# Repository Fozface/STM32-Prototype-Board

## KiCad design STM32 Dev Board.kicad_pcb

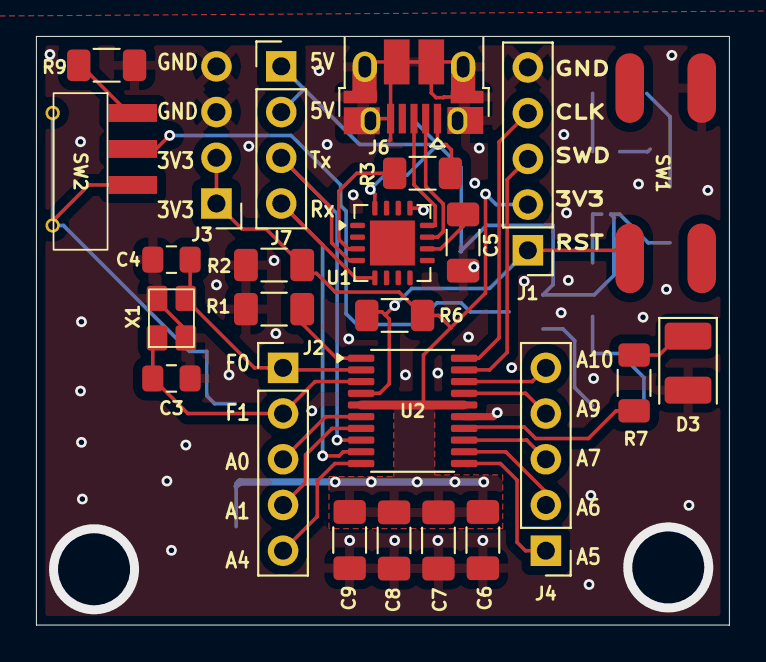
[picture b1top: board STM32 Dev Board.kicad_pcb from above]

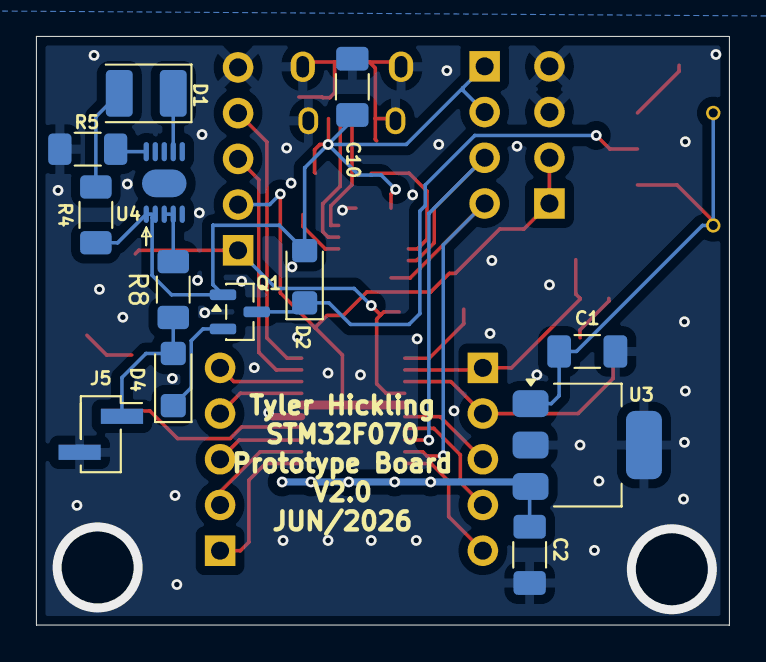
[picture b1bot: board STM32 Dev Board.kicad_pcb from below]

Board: 2 copper layers, 38.5 x 32.7 mm, 38 parts (13 on the bottom side), 34 nets.

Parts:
C1, C7: 4.7uF; C_1206_3216Metric_Pad1.33x1.80mm_HandSolder
C2: 1uF; C_1206_3216Metric_Pad1.33x1.80mm_HandSolder
C3, C4: 7pF; C_0805_2012Metric_Pad1.18x1.45mm_HandSolder
C5: 0.22-0.47u; C_1206_3216Metric_Pad1.33x1.80mm_HandSolder
C6: 100nF; C_1206_3216Metric_Pad1.33x1.80mm_HandSolder
C8: 10nF; C_1206_3216Metric_Pad1.33x1.80mm_HandSolder
C9: 1u; C_1206_3216Metric_Pad1.33x1.80mm_HandSolder
C10: 5u; C_1206_3216Metric_Pad1.33x1.80mm_HandSolder
D1: LED; LED_PLCC-2_3.4x3.0mm_KA
D2: D_Schottky; D_SMF
D3: LED; LED_PLCC-2_3.4x3.0mm_AK
D4: V1FM10-M3/H; D_SMF
J1, J2, J4: PinHeader_1x05_P2.54mm_Vertical
J3, J7: PinHeader_1x04_P2.54mm_Vertical
J5: 2 Pin JST; PinHeader_1x02_P2.00mm_Vertical_SMD_Pin1Right
J6: USB_B_Micro; USB_Micro-B_Amphenol_10103594-0001LF_Horizontal
Q1: PMOS; SOT-23
R1: 10k; C_1206_3216Metric_Pad1.33x1.80mm_HandSolder
R2: 0; C_1206_3216Metric_Pad1.33x1.80mm_HandSolder
R3, R6, R9: 10k; R_1206_3216Metric_Pad1.30x1.75mm_HandSolder
R4: 250; R_1206_3216Metric_Pad1.30x1.75mm_HandSolder
R5: 6.2k; R_1206_3216Metric_Pad1.30x1.75mm_HandSolder
R7: 330; R_1206_3216Metric_Pad1.30x1.75mm_HandSolder
R8: 0; R_1206_3216Metric_Pad1.30x1.75mm_HandSolder
SW1: SMT button KT Series top
SW2: 450405020524 SW
U1: MCP2221A-I/ML; QFN-16-1EP_4x4mm_P0.65mm_EP2.5x2.5mm
U2: STM32F070F6Px; TSSOP-20_4.4x6.5mm_P0.65mm
U3: MCP1824S; SOT-223-3_TabPin2
U4: MCP73113
X1: Xtal

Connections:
3.3V: C2.1, C6.1, C7.1, C8.1, C9.1, J1.2, J3.1, J3.2, R2.1, R6.1, U2.5 (VDDA), U2.16 (VDD), U3.3 (VO)
/MCU/SWCLK: J1.4, U2.20 (PA14)
/MCU/SWD: J1.3, U2.19 (PA13)
/PSU/BAT+: R8.1, U4.3 (VBAT), U4.4 (VBAT)
/PSU/STAT: D1.1 (K), U4.7 (STAT)
GND: C1.2, C2.2, C3.2, C4.1, C5.2, C6.2, C7.2, C8.2, C9.2, C10.2, D3.1 (K), J1.5, J3.3, J3.4, J5.2, J6.5 (GND), J6.6 (Shield), R1.1, R2.2, R5.2, R9.2, SW1.1, U1.13 (VSS), U2.15 (VSS), U3.2 (GND), U4.8 (VSS), U4.9 (VSS), X1.2 (GND), X1.4 (GND)
unnamed: D1.2 (A), R4.1
unnamed: D2.1 (K), Q1.1 (D), SW2.2
unnamed: D3.2 (A), R7.1
unnamed: D4.2 (A), J5.1, R8.2
unnamed: D4.1 (K), Q1.3 (S)
unnamed: J6.3 (D+), U1.12 (D+)
unnamed: J6.2 (D-), U1.11 (D-)
unnamed: R9.1, SW2.1
unnamed: C1.1, SW2.3 (C), SW2.4 (MNT), U3.1 (VI)
unnamed: C5.1, U1.10 (VUSB)
unnamed: R3.1, U1.3 (~RST)
unnamed: R1.2, U2.1 (BOOT0)
unnamed: J1.1, R6.2, SW1.4, U2.4 (NRST)
unnamed: J2.3, U2.6 (PA0)
unnamed: J2.4, U2.7 (PA1)
unnamed: J2.5, U2.10 (PA4)
unnamed: J4.1, U2.11 (PA5)
unnamed: J4.2, U2.12 (PA6)
unnamed: J4.3, U2.13 (PA7)
unnamed: J4.4, U2.17 (PA9/PA11)
unnamed: J4.5, U2.18 (PA10/PA12)
unnamed: R7.2, U2.14 (PB1)
unnamed: C4.2, J2.1, U2.2 (PF0), X1.3 (Xtal)
unnamed: C3.1, J2.2, U2.3 (PF1), X1.1 (Xtal)
unnamed: R5.1, U4.10 (PROG)
UART_Rx: J7.4, U1.5 (UTx), U2.9 (PA3)
UART_Tx: J7.3, U1.4 (URx), U2.8 (PA2)
VUSB: C10.1, D2.2 (A), J6.1 (VBUS), J7.1, J7.2, Q1.2 (G), R3.2, R4.2, U1.16 (VDD), U4.1 (VDD), U4.2 (VDD)

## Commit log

2026-06-22 Init Commit
2026-06-22 generated BOM
2026-06-22 generated drill and gerber files, updeted a few datasheets
2026-06-22 added gerber and drill files
2026-06-22 added ground via for UART-USB, updated gerber and drill files
2026-06-22 changed R8 FP to match component
2026-06-22 moved R8 designator on PCB to non obstructed location
2026-06-23 changed power supply of USB to UART to match datasheet, added changes to pcb Signed-off-by: Fozface <tyler.hickling99@gmail.com>
2026-06-23 repour ground on pcb
2026-06-24 slight changes to pcb, fixed u4 grounding
